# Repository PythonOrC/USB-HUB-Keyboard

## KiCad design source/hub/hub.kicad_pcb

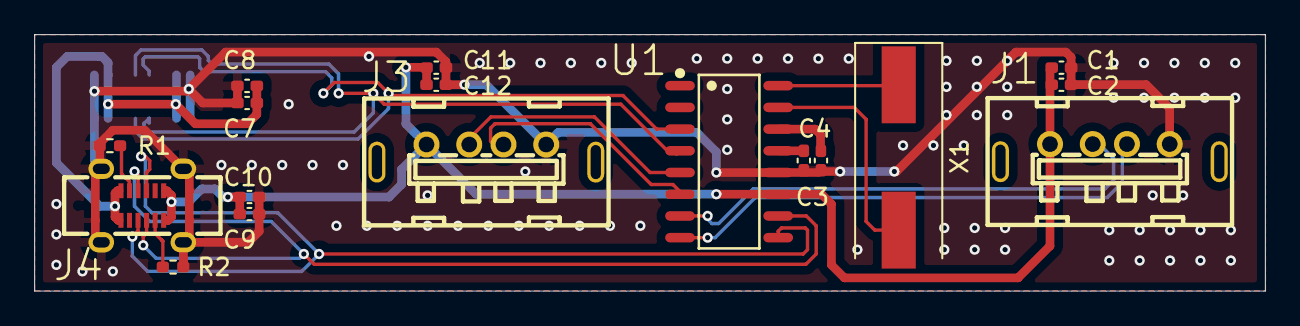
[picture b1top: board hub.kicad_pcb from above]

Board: 2 copper layers, 72.0 x 15.0 mm, 18 parts (1 on the bottom side), 16 nets.

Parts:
C1, C3, C4, C7, C9, C11: 10 uF; C_0402_1005Metric_Pad0.74x0.62mm_HandSolder
C2, C8, C10, C12: 0.1 uF; C_0402_1005Metric_Pad0.74x0.62mm_HandSolder
J1, J3: 10.0 180° ZCJB-HJ; USB-A-FEMALE
J2: 918-118A2021Y40002; TYPE-C-SMD-MALE
J4: TYPEC-303-ACP16; USB-C-SMD_TYPEC-303-ACP16
R1, R2: 5.1k; R_0402_1005Metric_Pad0.72x0.64mm_HandSolder
U1: SL2.1A; SOP-16_L10.0-W3.9-P1.27-LS6.0-BL
X1: 12 MHz; Crystal_SMD_HC49-SD

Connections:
+5V: C1.1, C2.1, C7.1, C8.1, C9.1, C10.1, C11.1, C12.1, J1.1 (VCC), J2.2 (V), J2.7 (V), J2.10 (V), J2.15 (V), J3.1 (VCC), J4.A4 (VBUS), J4.A9 (VBUS), J4.B4 (VBUS), J4.B9 (VBUS), U1.11 (VDD5)
/DM: J4.A7 (DN1), J4.B7 (DN2), U1.9 (DM)
/DM1: J1.2 (D-), U1.7 (DM1)
/DM2: J3.2 (D-), U1.5 (DM2)
/DM3: J2.4 (D-), J2.13 (D-), U1.3 (DM3)
/DP: J4.A6 (DP1), J4.B6 (DP2), U1.10 (DP)
/DP1: J1.3 (D+), U1.8 (DP1)
/DP2: J3.3 (D+), U1.6 (DP2)
/DP3: J2.5 (D+), J2.12 (D+), U1.4 (DP3)
Earth: C1.2, C2.2, C3.2, C4.2, C7.2, C8.2, C9.2, C10.2, C11.2, C12.2, J1.4 (GND), J2.1 (G), J2.8 (G), J2.9 (G), J2.16 (G), J3.4 (GND), J4.1 (GND), J4.2 (GND), J4.3 (GND), J4.4 (GND), J4.A1 (GND), J4.A12 (GND), J4.B1 (GND), J4.B12 (GND), R1.1, R2.1, U1.12 (GND)
unnamed: J4.A5 (CC1), R1.2
unnamed: J4.B5 (CC2), R2.2
unnamed: C3.1, U1.14 (VDD18)
unnamed: C4.1, U1.13 (VDD33)
unnamed: U1.16 (XIN), X1.1
unnamed: U1.15 (XOUT), X1.2

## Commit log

2025-04-11 added reference to other projects
2025-04-12 uploaded symbols
2025-04-14 finish sch and pcb
2025-04-15 finished redesigning
2025-04-15 updated missing routes
2025-04-15 add name and contact
2025-04-15 add copper zone
2025-04-15 added gnd vias copper pour
